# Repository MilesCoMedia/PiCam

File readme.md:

<h1 align="center">PiCam + PiCam Connect</h1>

> 

<div align="center">

</div>

## **Introduction**

PiCam is a fully open-source and budget-friendly dashcam system designed for seamless integration into any vehicle.  Unlike proprietary dashcam solutions, PiCam leverages the power and flexibility of the Raspberry Pi, making it an accessible and customizable option for drivers seeking reliable video recording and potentially other advanced features.  Because it's open source, users have complete control over the software and hardware, allowing them to tailor the system to their specific needs and contribute to its ongoing development.  The affordability of PiCam stems from its use of readily available components and the absence of licensing fees typically associated with commercial dashcam products.  This combination of open-source nature, affordability, and ease of integration makes PiCam an attractive alternative for those looking for a versatile and cost-effective dashcam solution.

 >### Note ###
> The "PiCam Connect iOS app and Hardware" is still under development. So, if you find any bugs or have any suggestion, feel free to post an issue or a pull request. [Post An Issue](https://github.com/MilesComedia/PiCam/issues/new)

> 

## **Getting Started**

Firstly, PiCam requires a **Raspberry Pi Zero**, A **Camera Module that supports PiCamera**, and a Minimum of **64GB Micro SD Card** as hardware.
PiCam will also need to have its **Micro SD Card** Flashed with the latest version of **Raspberry Pi OS Lite (Bullsye)**. You can use Raspberry Pi Imager for this: [Raspberry Pi Imager](https://www.raspberrypi.com/software/).

### Step 1
**1A**
Install Raspberry Pi OS Lite (Bullsye) Edition onto an Micro SD Card using Raspberry Pi Imager. [Windows Download](https://downloads.raspberrypi.org/imager/imager_latest.exe) [MacOS Download](https://downloads.raspberrypi.org/imager/imager_latest.dmg)
1. Click 'Choose OS' and find select 'Raspberry Pi OS (Other)'.
2. Find and select 'Raspberry Pi OS Lite (32 BIT)' or 'Raspberry Pi OS Lite (64 BIT)'
3. Insert your SD Card and select 'Choose Storage' then select your MicroSD Card.
4. Click 'NEXT' and an Options Menu will show, set the 'Hostname' to 'PiCam', and set both the 'Username' and 'Password' to 'picam' (all lowercase)
5. Then configure your Wi-Fi Network's SSID and Password.
6. Then click 'SAVE' and click 'Write'. The Imager will begin to write the OS to the Micro SD card.
> [!WARNING]
> **DO NOT UNPLUG THE SD CARD OR CLOSE THE IMAGER UNTIL IT INDICATES THE WRITE IS COMPLETE, Doing so could corrupt the SD Card.**

> [!NOTE]
> You may need to use a MicroSD card adapter to insert the SD Card into your Computer.

> [!IMPORTANT]
> Your Micro SD Card may display as 'Generic Media Device (CAPACITY e.g 64GB)'. To ensure you are selecting the right storage device, compare the storage capacity on the SD Card to what is displayed.

**1B**
> You may need to use a MicroSD card adapter to insert the SD Card into your Computer
Once you have installed Raspberry Pi OS Lite onto the SD Card, insert the MicroSD into the MicroSD card slot on a Raspberry Pi (Zero, Zero W, or 3A+ or newer) and attach a compatible Raspberry Pi Camera [List of Compatible Cameras](enter link).
Then plug in a Micro USB cable to the Raspberry Pi's **POWER or PWR** Port, then power it on.

### Step 2

**2A**
Ensure your Raspberry Pi booted correctly plug a HDMI cable into your Raspberry Pi, if the Raspberry Pi displays 
> You may need to use a Mini HDMI to HDMI adapter 
**Install required Packages and Dependencies*

Firs
```bash

```
```bash

# Navigate to the project directory
cd my-awesome-project

# Create a virtual environment (recommended)
python3 -m venv venv
source venv/bin/activate  # On Windows: venv\Scripts\activate

# Install dependencies
pip install -r requirements.txt

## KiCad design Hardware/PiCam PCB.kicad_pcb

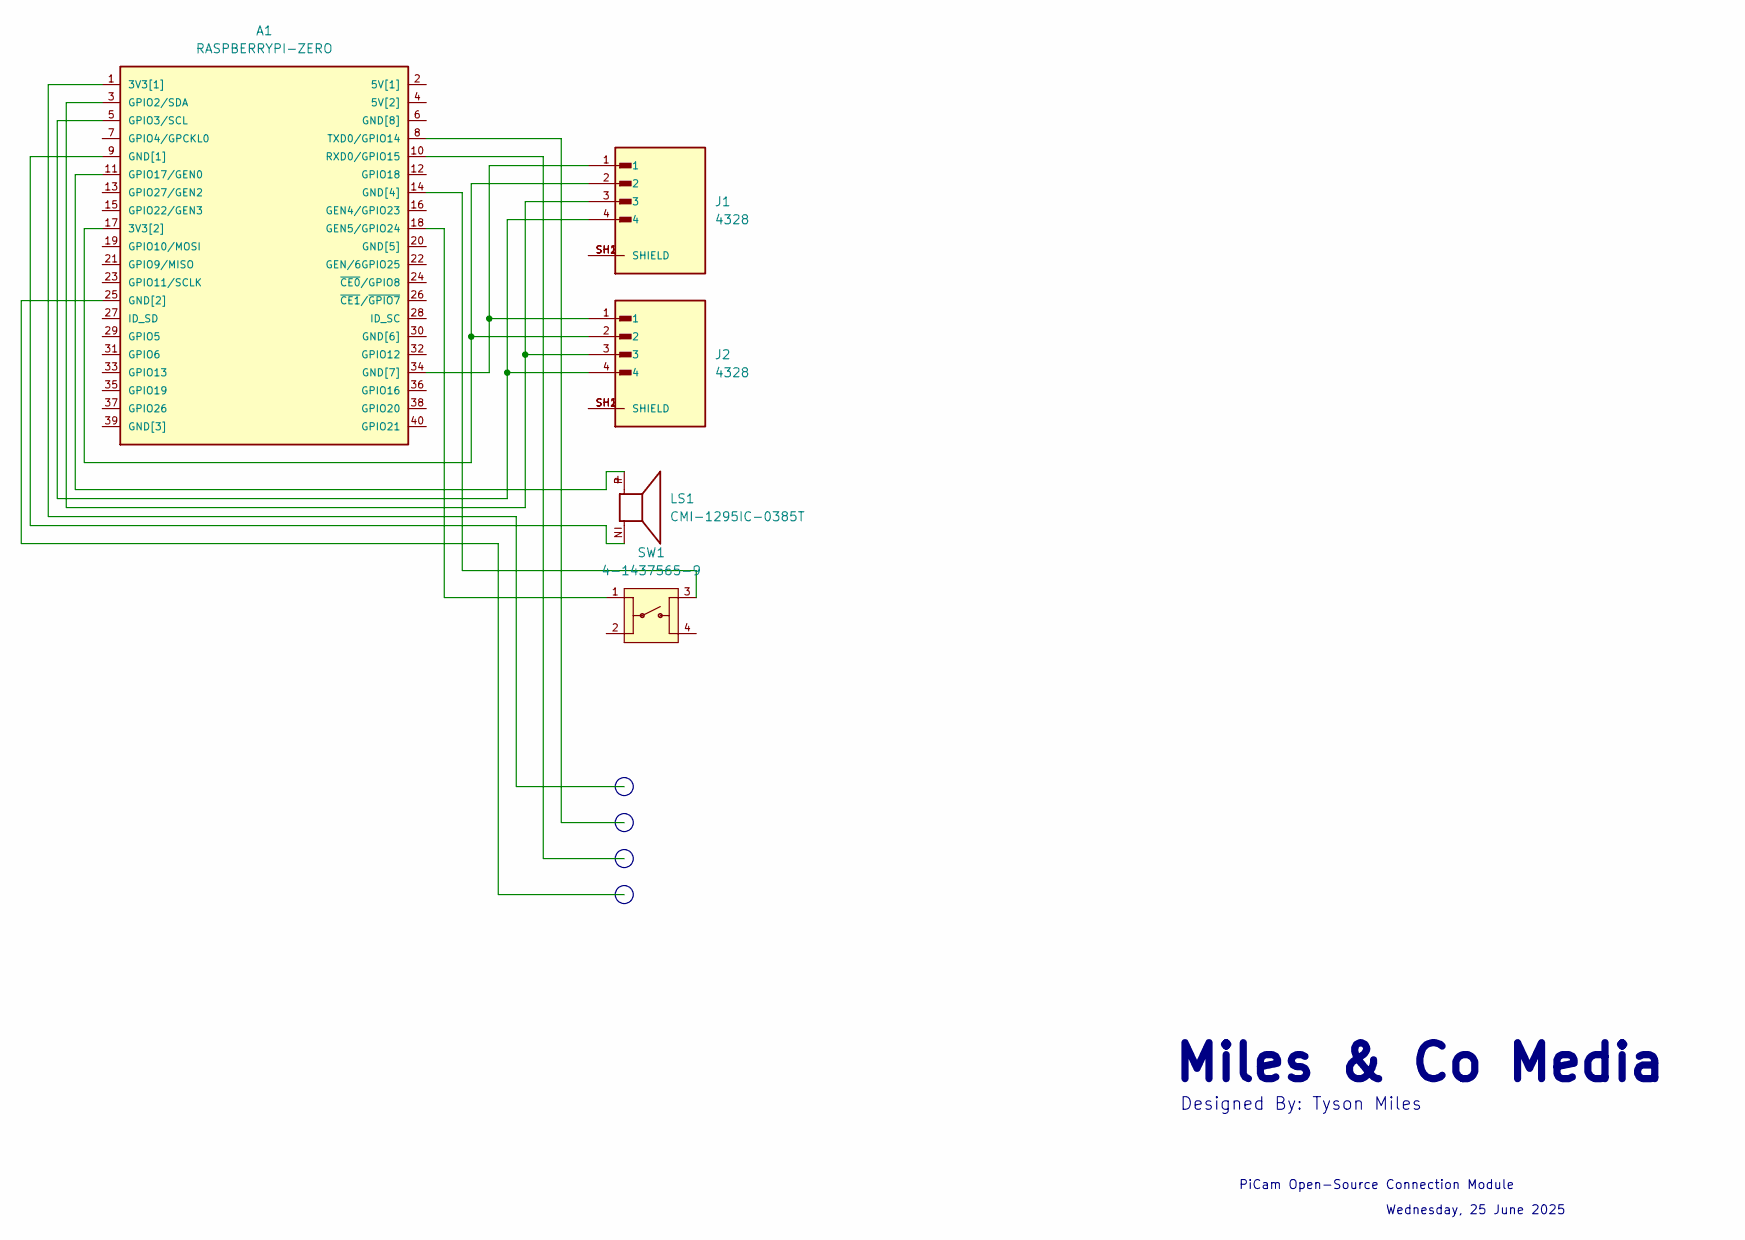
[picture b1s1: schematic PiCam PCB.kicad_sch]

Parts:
A1: RASPBERRYPI-ZERO; RASPBERRYPI-ZERO_RPI-ZERO
J1, J2: 4328; ADAFRUIT_4328; PARTREV 23/3/21
LS1: CMI-1295IC-0385T; CUI_CMI-1295IC-0385T; PARTREV 1.0
SW1: 4-1437565-9; TE_4-1437565-9; PARTREV V

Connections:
unnamed: A1.17 (3V3[2]), J1.2, J2.2
unnamed: A1.18 (GEN5/GPIO24), SW1.1
unnamed: A1.9 (GND[1]), LS1.N
unnamed: A1.14 (GND[4]), SW1.3
unnamed: A1.34 (GND[7]), J1.1, J2.1
unnamed: A1.3 (GPIO2/SDA), J1.3, J2.3
unnamed: A1.5 (GPIO3/SCL), J1.4, J2.4
unnamed: A1.11 (GPIO17/GEN0), LS1.P
unnamed: J1.SH1 (SHIELD), J1.SH2 (SHIELD)
unnamed: J2.SH1 (SHIELD), J2.SH2 (SHIELD)

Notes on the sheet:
Wednesday, 25 June 2025
PiCam Open-Source Connection Module
Miles & Co Media
Designed By: Tyson Miles

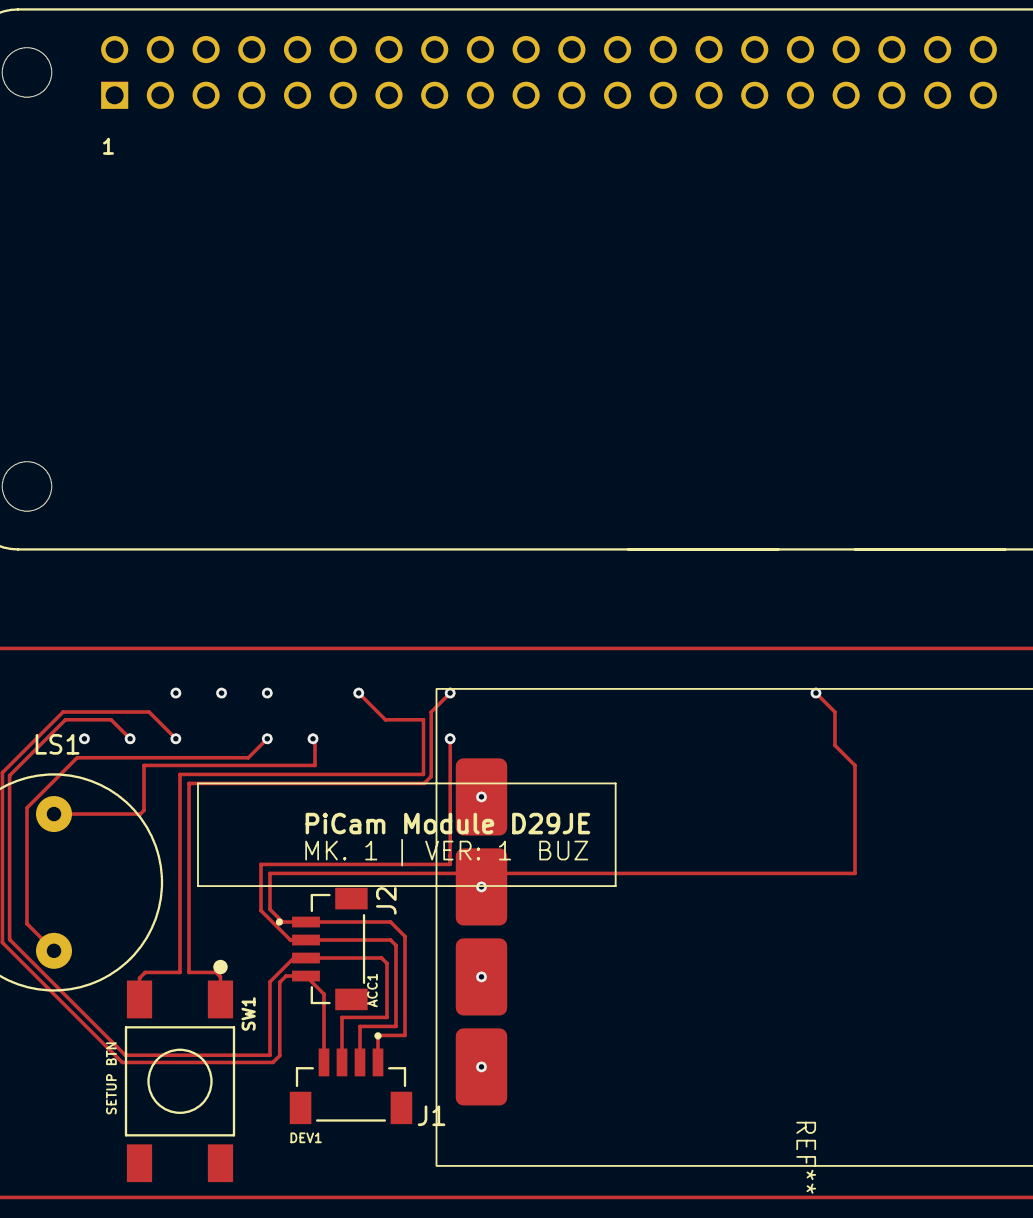
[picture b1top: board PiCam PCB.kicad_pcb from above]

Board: 2 copper layers, 5 parts (0 on the bottom side), 10 nets.

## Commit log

2025-02-17 Added Picam image
2025-02-18 Create Licence
2025-03-30 Update issue templates
2025-04-17 Update Licence
2025-04-17 UPDATE LICENSE
2025-04-17 Create LICENSE
2025-04-26 Create iOS Bug Report
2025-05-24 Create Main
2025-05-24 Create Beta
2025-05-25 Rename LICENSE to Apache Licence
2025-05-25 Rename Apache Licence to LICENCE
2025-05-25 Rename LICENCE to LICENCE-Apache Licence
2025-05-25 Add Alpha Test Files from Prototype
2025-05-25 Rename Untitled design-4.png to CONNECTLGO.png
2025-05-25 Rename Untitled design-7.png to CONNECTLGOICON.png
2025-05-25 Create Base
2025-05-26 Rename LICENCE-Apache Licence to LICENCE
2025-07-04 Create hardware
